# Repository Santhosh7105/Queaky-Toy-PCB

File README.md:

# Queaky Toy PCB

A custom single-layer PCB designed and fabricated using **KiCad** for a **555 Timer IC based touch-activated electronic toy**.

This project demonstrates the complete PCB design workflow, from schematic capture to PCB fabrication and hardware testing.

---

# 📖 Overview

The Queaky Toy is a simple electronic circuit that generates a sound when the touch input is activated. The PCB was designed in KiCad and fabricated using a CNC PCB milling machine.

This project was created to gain hands-on experience in PCB design, fabrication, soldering, and electronic hardware development.

---

# ✨ Features

* Single Layer PCB Design
* Designed using KiCad
* 555 Timer IC Based Circuit
* Touch Activated Input
* Buzzer Output
* CNC PCB Fabrication
* Through-Hole Components

---

# 🛠 Tools Used

* KiCad
* FlatCAM
* LinuxCNC
* CNC PCB Milling Machine

---

# 📷 Project Images

## Schematic

---

## PCB Layout

---

## PCB 3D View

---

## CNC Fabrication Routing

---

## Fabricated PCB

---

## Working Prototype

---

# ⚙ Working Principle

The touch sensor provides a trigger signal to the 555 Timer IC. Once triggered, the timer generates an output signal that drives the buzzer, producing a sound. The circuit is powered using a 9V battery.

---

# 📂 Repository Contents

* KiCad Project Files
* Schematic
* PCB Layout
* PCB Design Files
* Project Images

---

# 🚀 Future Improvements

* Double Layer PCB Design
* SMD Version
* Compact PCB Layout
* Improved Touch Sensitivity

---

# 👨‍💻 Author

**Santhosh S**

Electronics & PCB Design Enthusiast

KiCad | PCB Design | CNC PCB Fabrication | Embedded Systems

---

⭐ If you like this project, feel free to star the repository.

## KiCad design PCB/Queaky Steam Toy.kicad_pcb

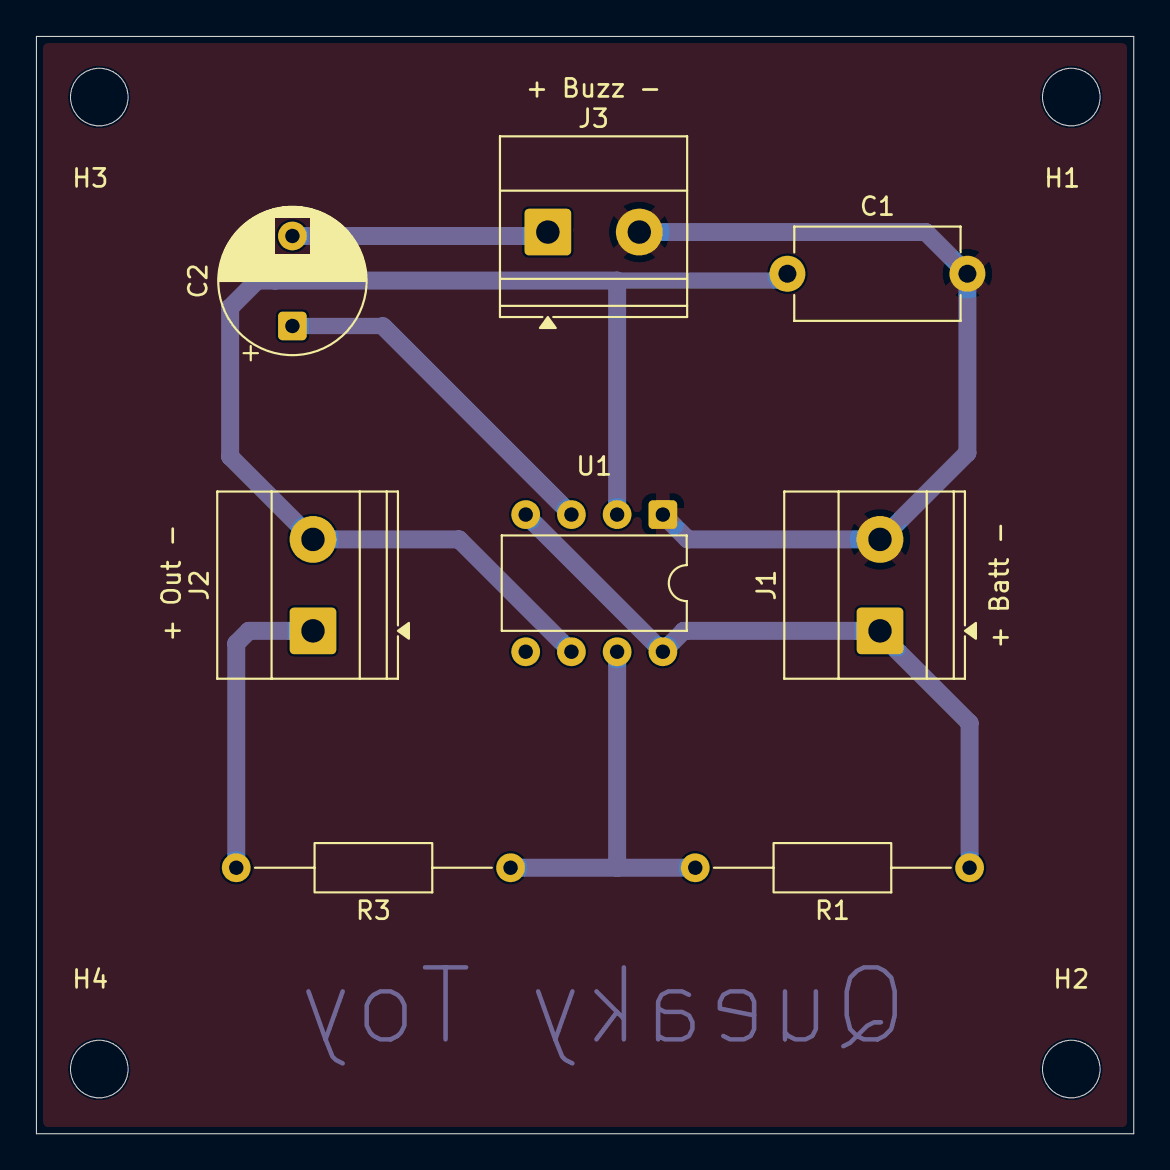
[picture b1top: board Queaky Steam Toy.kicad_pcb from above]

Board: 2 copper layers, 61.0 x 61.0 mm, 12 parts (0 on the bottom side), 7 nets.

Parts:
C1: 1nf; C_Disc_D9.0mm_W5.0mm_P10.00mm
C2: 100uf1; CP_Radial_D8.0mm_P5.00mm
H1, H2, H3, H4: MountingHole; MountingHole_3.2mm_M3
J1: + Batt -; TerminalBlock_Phoenix_MKDS-1,5-2-5.08_1x02_P5.08mm_Horizont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
J2: + Out -; TerminalBlock_Phoenix_MKDS-1,5-2-5.08_1x02_P5.08mm_Horizont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
J3: + Buzz -; TerminalBlock_Phoenix_MKDS-1,5-2-5.08_1x02_P5.08mm_Horizont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
R1: 1k; R_Axial_DIN0207_L6.3mm_D2.5mm_P15.24mm_Horizontal
R3: 10k; R_Axial_DIN0207_L6.3mm_D2.5mm_P15.24mm_Horizontal
U1: NE555P; DIP-8_W7.62mm

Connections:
/DIS: R1.2, R3.1, U1.7 (DIS)
/TR: C1.1, J2.2, U1.2 (TR), U1.6 (THR)
/out: C2.1, U1.3 (Q)
GND: C1.2, J1.2, J3.2, U1.1 (GND)
unnamed: J2.1, R3.2
unnamed: C2.2, J3.1
VCC: J1.1, R1.1, U1.4 (R), U1.8 (VCC)
